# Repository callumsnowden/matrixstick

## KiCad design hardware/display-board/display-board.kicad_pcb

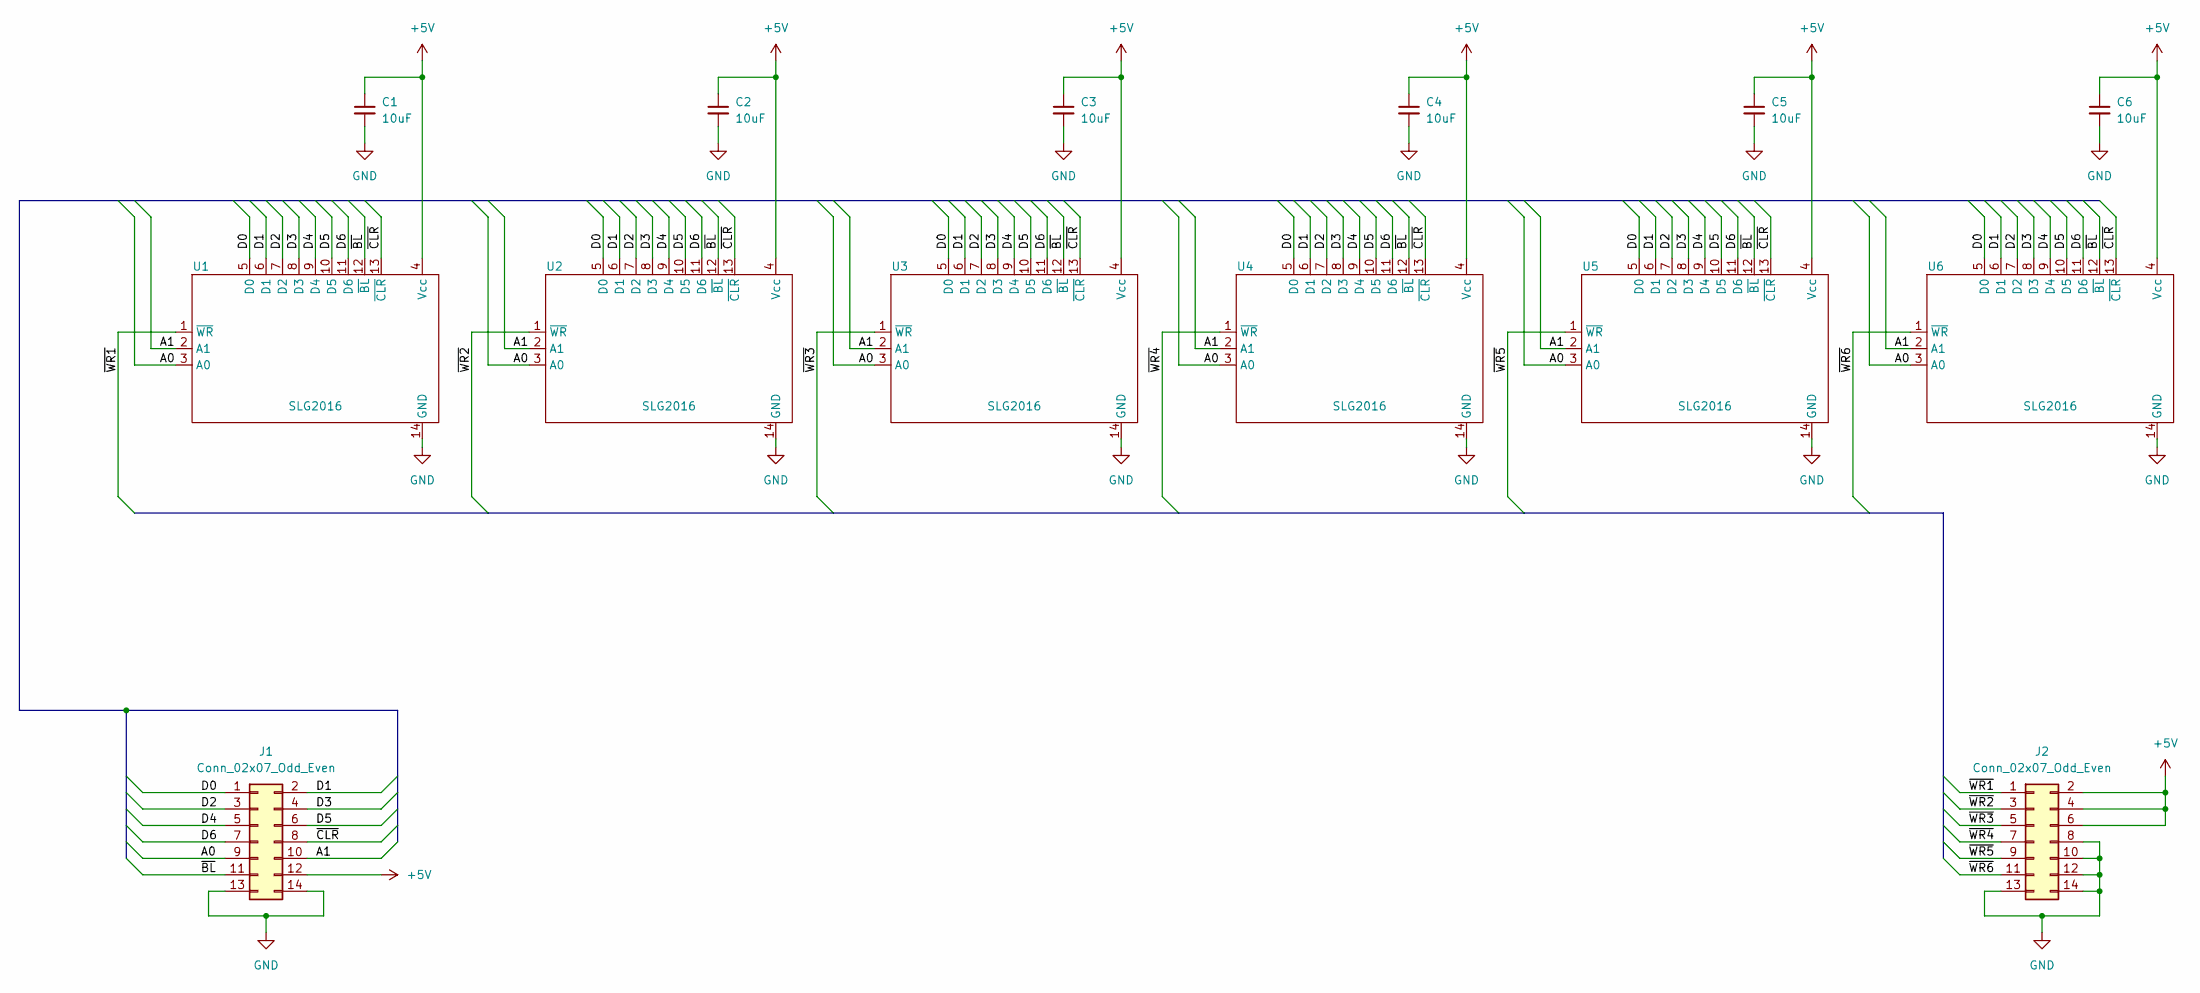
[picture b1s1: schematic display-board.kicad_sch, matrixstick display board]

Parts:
C1, C2, C3, C4, C5, C6: 10uF; C_0603_1608Metric
J1, J2: Conn_02x07_Odd_Even; PinHeader_2x07_P2.54mm_Vertical
U1, U2, U3, U4, U5, U6: SLG2016; SLX2016

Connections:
+5V: C1.1, C2.1, C3.1, C4.1, C5.1, C6.1, J1.12, J2.2, J2.4, J2.6, U1.4 (Vcc), U2.4 (Vcc), U3.4 (Vcc), U4.4 (Vcc), U5.4 (Vcc), U6.4 (Vcc)
/A0: J1.9, U1.3 (A0), U2.3 (A0), U3.3 (A0), U4.3 (A0), U5.3 (A0), U6.3 (A0)
/A1: J1.10, U1.2 (A1), U2.2 (A1), U3.2 (A1), U4.2 (A1), U5.2 (A1), U6.2 (A1)
/D0: J1.1, U1.5 (D0), U2.5 (D0), U3.5 (D0), U4.5 (D0), U5.5 (D0), U6.5 (D0)
/D1: J1.2, U1.6 (D1), U2.6 (D1), U3.6 (D1), U4.6 (D1), U5.6 (D1), U6.6 (D1)
/D2: J1.3, U1.7 (D2), U2.7 (D2), U3.7 (D2), U4.7 (D2), U5.7 (D2), U6.7 (D2)
/D3: J1.4, U1.8 (D3), U2.8 (D3), U3.8 (D3), U4.8 (D3), U5.8 (D3), U6.8 (D3)
/D4: J1.5, U1.9 (D4), U2.9 (D4), U3.9 (D4), U4.9 (D4), U5.9 (D4), U6.9 (D4)
/D5: J1.6, U1.10 (D5), U2.10 (D5), U3.10 (D5), U4.10 (D5), U5.10 (D5), U6.10 (D5)
/D6: J1.7, U1.11 (D6), U2.11 (D6), U3.11 (D6), U4.11 (D6), U5.11 (D6), U6.11 (D6)
/~BL: J1.11, U1.12 (~BL), U2.12 (~BL), U3.12 (~BL), U4.12 (~BL), U5.12 (~BL), U6.12 (~BL)
/~CLR: J1.8, U1.13 (~CLR), U2.13 (~CLR), U3.13 (~CLR), U4.13 (~CLR), U5.13 (~CLR), U6.13 (~CLR)
/~WR1: J2.1, U1.1 (~WR)
/~WR2: J2.3, U2.1 (~WR)
/~WR3: J2.5, U3.1 (~WR)
/~WR4: J2.7, U4.1 (~WR)
/~WR5: J2.9, U5.1 (~WR)
/~WR6: J2.11, U6.1 (~WR)
GND: C1.2, C2.2, C3.2, C4.2, C5.2, C6.2, J1.13, J1.14, J2.8, J2.10, J2.12, J2.13, J2.14, U1.14 (GND), U2.14 (GND), U3.14 (GND), U4.14 (GND), U5.14 (GND), U6.14 (GND)

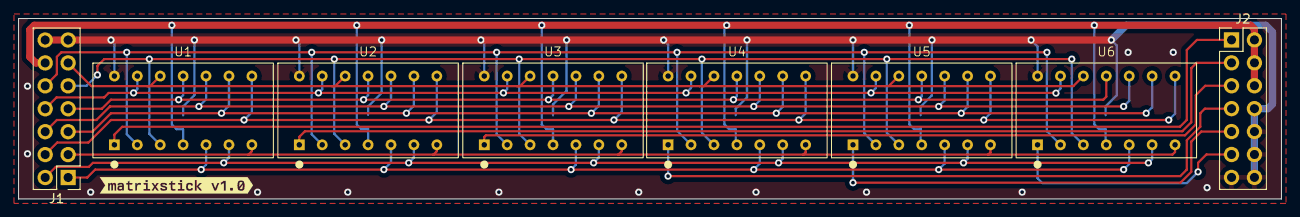
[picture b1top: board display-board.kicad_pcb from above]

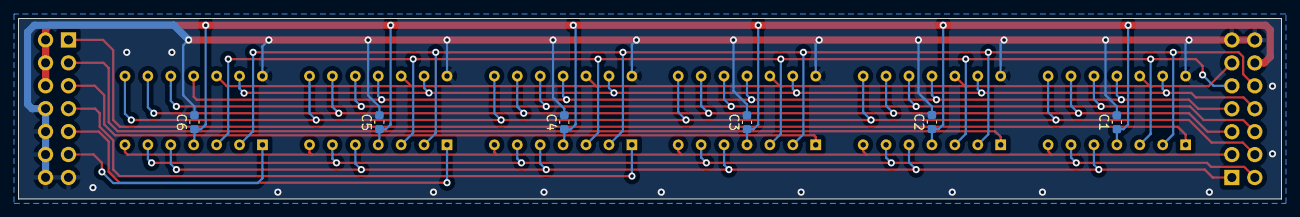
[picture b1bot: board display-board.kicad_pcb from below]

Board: 2 copper layers, 140.0 x 20.0 mm, 15 parts (6 on the bottom side), 19 nets.

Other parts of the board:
kibuzzard-668E653B: G***; kibuzzard-668E653B

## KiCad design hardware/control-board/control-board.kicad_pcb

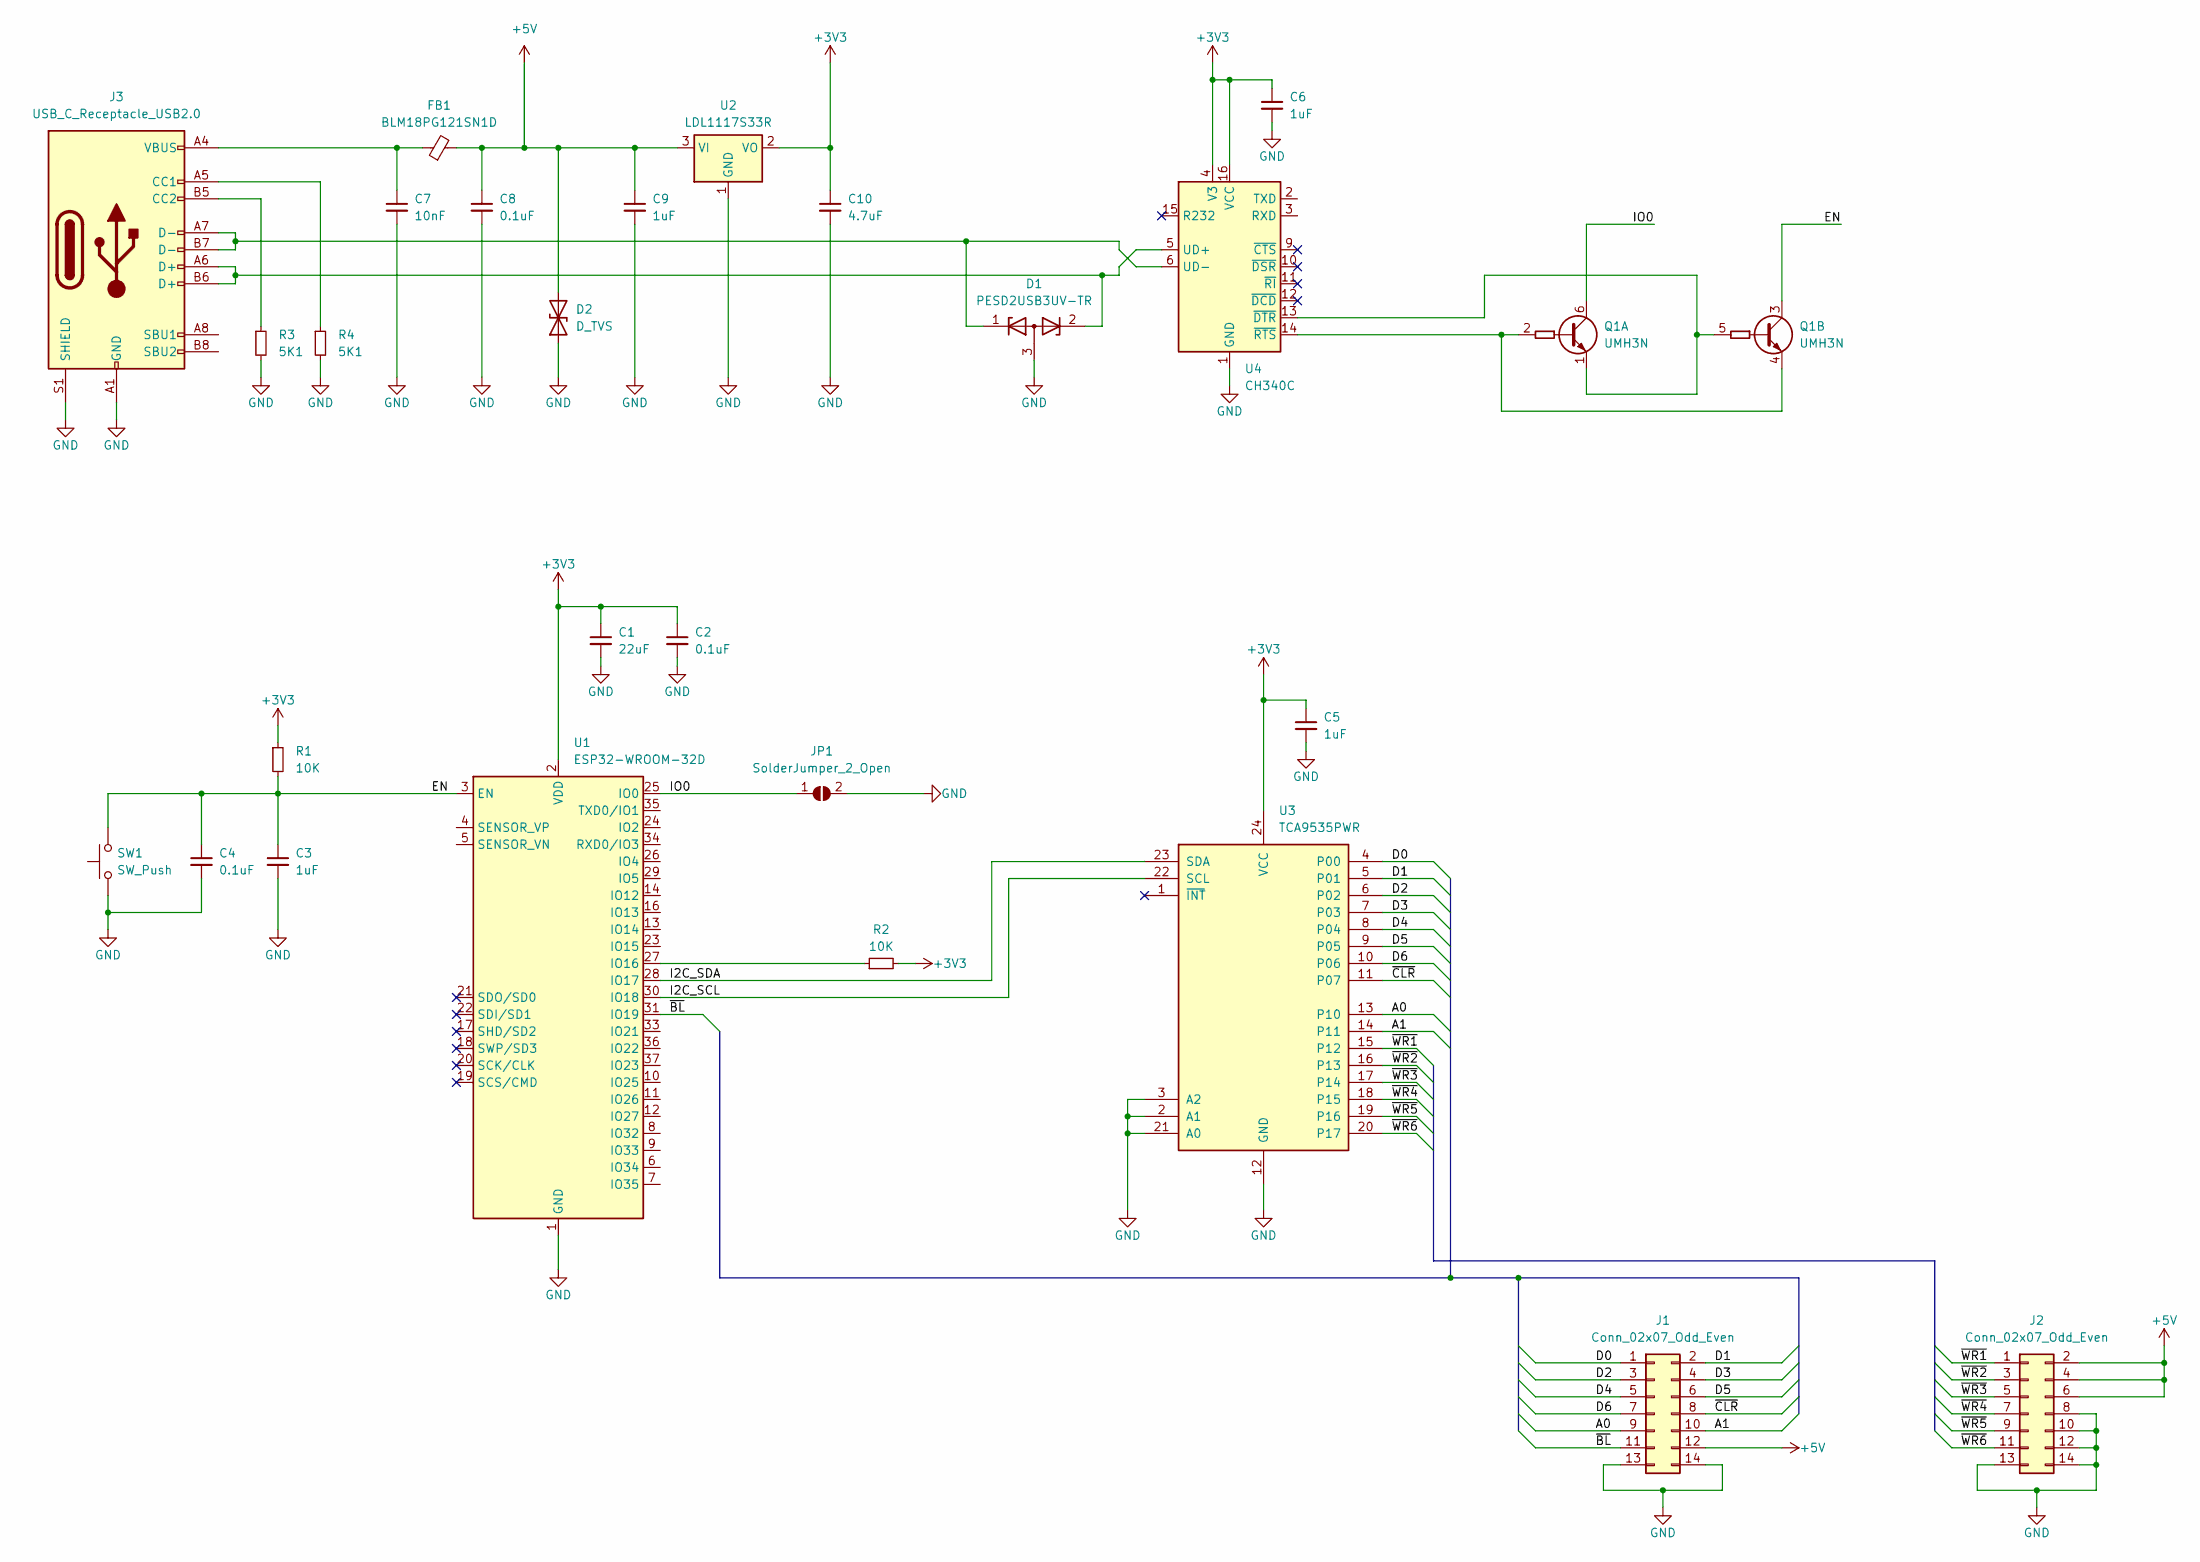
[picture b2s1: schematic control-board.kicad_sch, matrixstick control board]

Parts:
C1: 22uF; C_1206_3216Metric
C2, C4, C8: 0.1uF; C_0603_1608Metric
C3, C5, C6, C9: 1uF; C_0603_1608Metric
C7: 10nF; C_0603_1608Metric
C10: 4.7uF; C_0805_2012Metric
D1: PESD2USB3UV-TR; SOT-23
D2: D_TVS; D_SMA
FB1: BLM18PG121SN1D; L_0603_1608Metric; ManufacturerPartNumber BLM18PG121SN1D
J1, J2: Conn_02x07_Odd_Even; PinHeader_2x07_P2.54mm_Vertical
J3: USB_C_Receptacle_USB2.0
JP1: SolderJumper_2_Open; SolderJumper-2_P1.3mm_Open_Pad1.0x1.5mm
Q1: UMH3N; SOT-363_SC-70-6
R1, R2: 10K; R_0603_1608Metric
R3, R4: 5K1; R_0603_1608Metric
SW1: SW_Push; SW_Push_1P1T_NO_6x6mm_H9.5mm
U1: ESP32-WROOM-32D
U2: LDL1117S33R; SOT-223-3_TabPin2
U3: TCA9535PWR; TSSOP-24_4.4x7.8mm_P0.65mm
U4: CH340C; SOIC-16_3.9x9.9mm_P1.27mm

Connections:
+3V3: C1.1, C2.1, C5.1, C6.1, C10.1, R1.1, R2.2, U1.2 (VDD), U2.2 (VO), U3.24 (VCC), U4.4 (V3), U4.16 (VCC)
+5V: C8.1, C9.1, D2.2 (A2), FB1.2, J1.12, J2.2, J2.4, J2.6, U2.3 (VI)
/A0: J1.9, U3.13 (P10)
/A1: J1.10, U3.14 (P11)
/D0: J1.1, U3.4 (P00)
/D1: J1.2, U3.5 (P01)
/D2: J1.3, U3.6 (P02)
/D3: J1.4, U3.7 (P03)
/D4: J1.5, U3.8 (P04)
/D5: J1.6, U3.9 (P05)
/D6: J1.7, U3.10 (P06)
/EN: C3.1, C4.1, Q1.3 (C2), R1.2, SW1.2, U1.3 (EN)
/I2C_SCL: U1.30 (IO18), U3.22 (SCL)
/I2C_SDA: U1.28 (IO17), U3.23 (SDA)
/IO0: JP1.1 (A), Q1.6 (C1), U1.25 (IO0)
/~BL: J1.11, U1.31 (IO19)
/~CLR: J1.8, U3.11 (P07)
/~WR1: J2.1, U3.15 (P12)
/~WR2: J2.3, U3.16 (P13)
/~WR3: J2.5, U3.17 (P14)
/~WR4: J2.7, U3.18 (P15)
/~WR5: J2.9, U3.19 (P16)
/~WR6: J2.11, U3.20 (P17)
GND: C1.2, C2.2, C3.2, C4.2, C5.2, C6.2, C7.2, C8.2, C9.2, C10.2, D1.3 (A), D2.1 (A1), J1.13, J1.14, J2.8, J2.10, J2.12, J2.13, J2.14, J3.A1 (GND), J3.A12 (GND), J3.B1 (GND), J3.B12 (GND), J3.S1 (SHIELD), JP1.2 (B), R3.2, R4.2, SW1.1, U1.1 (GND), U1.15 (GND), U1.38 (GND), U1.39 (GND), U2.1 (GND), U3.2 (A1), U3.3 (A2), U3.12 (GND), U3.21 (A0), U4.1 (GND)
unnamed: C7.1, FB1.1, J3.A4 (VBUS), J3.A9 (VBUS), J3.B4 (VBUS), J3.B9 (VBUS)
unnamed: J3.A5 (CC1), R4.1
unnamed: J3.B5 (CC2), R3.1
unnamed: Q1.2 (B1), Q1.4 (E2), U4.14 (~RTS)
unnamed: Q1.1 (E1), Q1.5 (B2), U4.13 (~DTR)
unnamed: R2.1, U1.27 (IO16)
unnamed: D1.2 (K), J3.A6 (D+), J3.B6 (D+), U4.5 (UD+)
unnamed: D1.1 (K), J3.A7 (D-), J3.B7 (D-), U4.6 (UD-)

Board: 2 copper layers, 27 parts (6 on the bottom side), 30 nets, no tracks yet.

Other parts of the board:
kibuzzard-668E653B: G***; kibuzzard-668E653B

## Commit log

2024-11-27 Add preliminary hardware design
